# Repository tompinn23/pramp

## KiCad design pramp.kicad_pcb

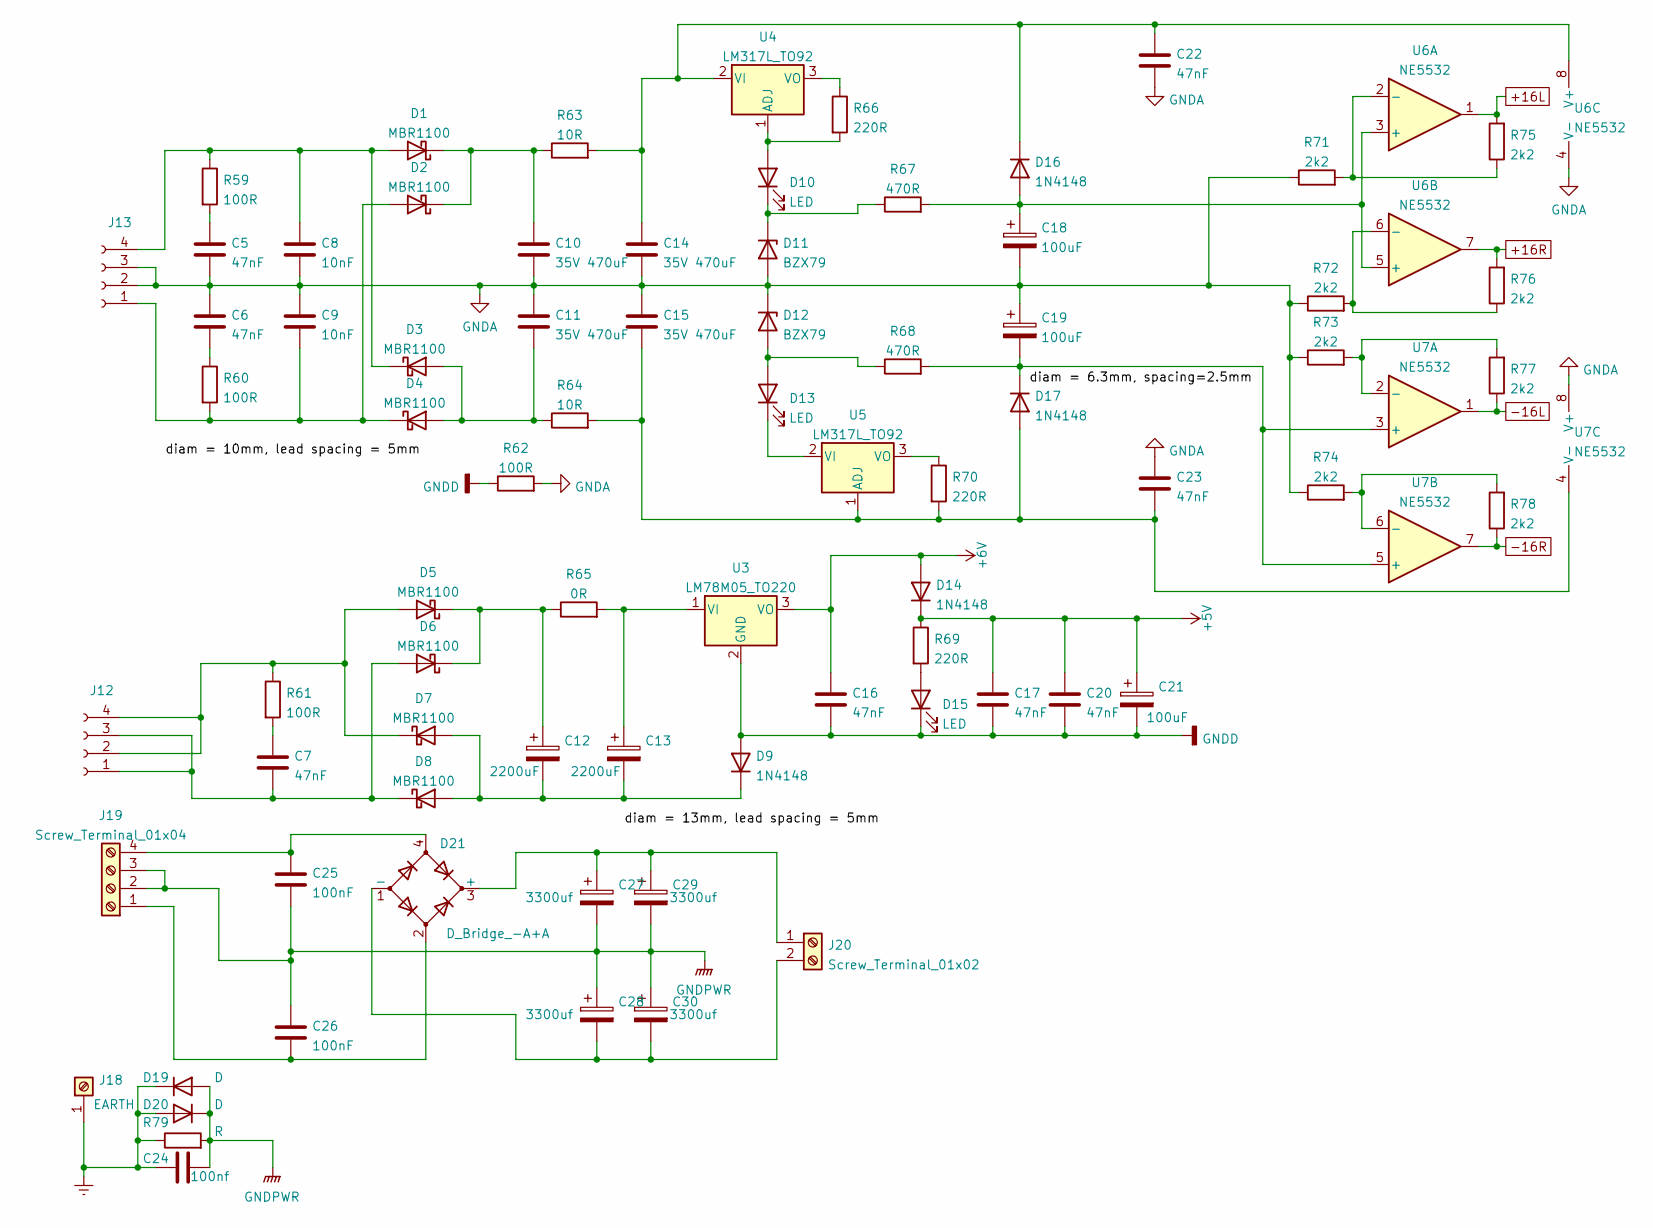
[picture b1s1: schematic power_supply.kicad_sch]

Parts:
C5, C6, C7, C16, C17, C20, C22, C23: 47nF; C_Disc_D3.8mm_W2.6mm_P2.50mm; Farnell part number 1216437
C8, C9: 10nF; C_Disc_D3.8mm_W2.6mm_P2.50mm; Farnell part number 1100380
C10, C11, C14, C15: 35V 470uF; CP_Radial_D10.0mm_P5.00mm; Farnell part number cpc
C12, C13: 2200uF; CP_Radial_D13.0mm_P5.00mm; Farnell part number 1219464
C18, C19, C21: 100uF; CP_Radial_D6.3mm_P2.50mm; Farnell part number 2841913
C24: 100nf; C_Disc_D16.0mm_W5.0mm_P10.00mm; Farnell part number 3289419
C25, C26: 100nF; C_Disc_D3.8mm_W2.6mm_P2.50mm; Farnell part number n.a
C27, C28, C29, C30: 3300uf; CP_Radial_D18.0mm_P7.50mm; Farnell part number n.a
D1, D2, D3, D4, D5, D6, D7, D8: MBR1100; D_DO-41_SOD81_P10.16mm_Horizontal; Farnell part number 1861419
D9, D14, D16, D17: 1N4148; D_DO-35_SOD27_P7.62mm_Horizontal; Farnell part number 1651145
D10, D13, D15: LED; LED_D3.0mm; Farnell part number 1142514
D11, D12: BZX79; D_DO-35_SOD27_P7.62mm_Horizontal; Farnell part number 1097241
D19, D20: D; TO-220-2_Vertical; Farnell part number 1885721
D21: D_Bridge_-A+A; Diode_Bridge_32.0x5.6x17.0mm_P10.0mm_P7.5mm; Farnell part number n.a
J12: 2x9v 7va; PinHeader_1x04_P2.54mm_Vertical
J13: 2x15v 4va; PinHeader_1x04_P2.54mm_Vertical
J18: EARTH; Pin_D1.0mm_L10.0mm_LooseFit; Farnell part number CN19743
J19: Screw_Terminal_01x04; JST_NV_B04P-NV_1x04_P5.00mm_Vertical; Farnell part number CN19747
J20: Screw_Terminal_01x02; JST_NV_B02P-NV_1x02_P5.00mm_Vertical
R59, R60, R61, R62: 100R; R_MELF_MMB-0207; Farnell part number 3086720
R63, R64: 10R; R_MELF_MMB-0207; Farnell part number 3086604
R65: 0R; R_MELF_MMB-0207; Farnell part number 3086471
R66, R69, R70: 220R; R_MELF_MMB-0207; Farnell part number 3086768
R67, R68: 470R; R_MELF_MMB-0207; Farnell part number 3086800
R71, R72, R73, R74, R75, R76, R77, R78: 2k2; R_MELF_MMB-0207; Farnell part number 3086884
R79: R; R_Axial_DIN0918_L18.0mm_D9.0mm_P25.40mm_Horizontal; Farnell part number 1735131
U3: LM78M05_TO220; TO-220-3_Horizontal_TabUp; Farnell part number 9666095
U4, U5: LM317L_TO92; TO-92_Inline; Farnell part number 3130111
U6, U7: NE5532; DIP-8_W7.62mm_Socket; Farnell part number 3117310

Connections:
+5V: C17.1, C20.1, C21.1, D14.1 (K), R69.1; also elsewhere on the board
+6V: C16.1, D14.2 (A), U3.3 (VO); also elsewhere on the board
+16L: R75.2, U6.1; also elsewhere on the board
+16R: R76.2, U6.7; also elsewhere on the board
-16L: R77.1, U7.1; also elsewhere on the board
-16R: R78.1, U7.7; also elsewhere on the board
Earth: C24.1, D19.1 (K), D20.2 (A), J18.1, R79.1
GNDA: C5.2, C6.1, C8.2, C9.1, C10.2, C11.1, C14.2, C15.1, C18.2, C19.1, C22.2, C23.1, D11.2 (A), D12.1 (K), J13.2, J13.3, R62.2, R71.1, R72.1, R73.1, R74.1, U6.4 (V-), U7.8 (V+); also elsewhere on the board
GNDD: C16.2, C17.2, C20.2, C21.2, D9.2 (A), D15.1 (K), R62.1, U3.2 (GND); also elsewhere on the board
GNDPWR: C24.2, C25.2, C26.1, C27.2, C28.1, C29.2, C30.1, D19.2 (A), D20.1 (K), J19.2, J19.3, R79.2
unnamed: C5.1, R59.2
unnamed: C6.2, R60.1
unnamed: C7.1, R61.2
unnamed: C7.2, D6.2 (A), D8.1 (K), J12.1, J12.3
unnamed: C8.1, D1.2 (A), D3.1 (K), J13.4, R59.1
unnamed: C9.2, D2.2 (A), D4.1 (K), J13.1, R60.2
unnamed: C10.1, D1.1 (K), D2.1 (K), R63.1
unnamed: C11.2, D3.2 (A), D4.2 (A), R64.1
unnamed: C12.1, D5.1 (K), D6.1 (K), R65.1
unnamed: C12.2, C13.2, D7.2 (A), D8.2 (A), D9.1 (K)
unnamed: C13.1, R65.2, U3.1 (VI)
unnamed: C14.1, C22.1, D16.1 (K), R63.2, U4.2 (VI), U6.8 (V+)
unnamed: C15.2, C23.2, D17.2 (A), R64.2, R70.2, U5.1 (ADJ), U7.4 (V-)
unnamed: C18.1, D16.2 (A), R67.2, U6.3 (+), U6.5 (+)
unnamed: C19.2, D17.1 (K), R68.2, U7.3 (+), U7.5 (+)
unnamed: C25.1, D21.4, J19.4
unnamed: C26.2, D21.2, J19.1
unnamed: C27.1, C29.1, D21.3 (+), J20.1
unnamed: C28.2, C30.2, D21.1 (-), J20.2
unnamed: D5.2 (A), D7.1 (K), J12.2, J12.4, R61.1
unnamed: D10.1 (K), D11.1 (K), R67.1
unnamed: D10.2 (A), R66.2, U4.1 (ADJ)
unnamed: D12.2 (A), D13.2 (A), R68.1
unnamed: D13.1 (K), U5.2 (VI)
unnamed: D15.2 (A), R69.2
unnamed: R66.1, U4.3 (VO)
unnamed: R70.1, U5.3 (VO)
unnamed: R71.2, R75.1, U6.2 (-)
unnamed: R72.2, R76.1, U6.6 (-)
unnamed: R73.2, R77.2, U7.2 (-)
unnamed: R74.2, R78.2, U7.6 (-)

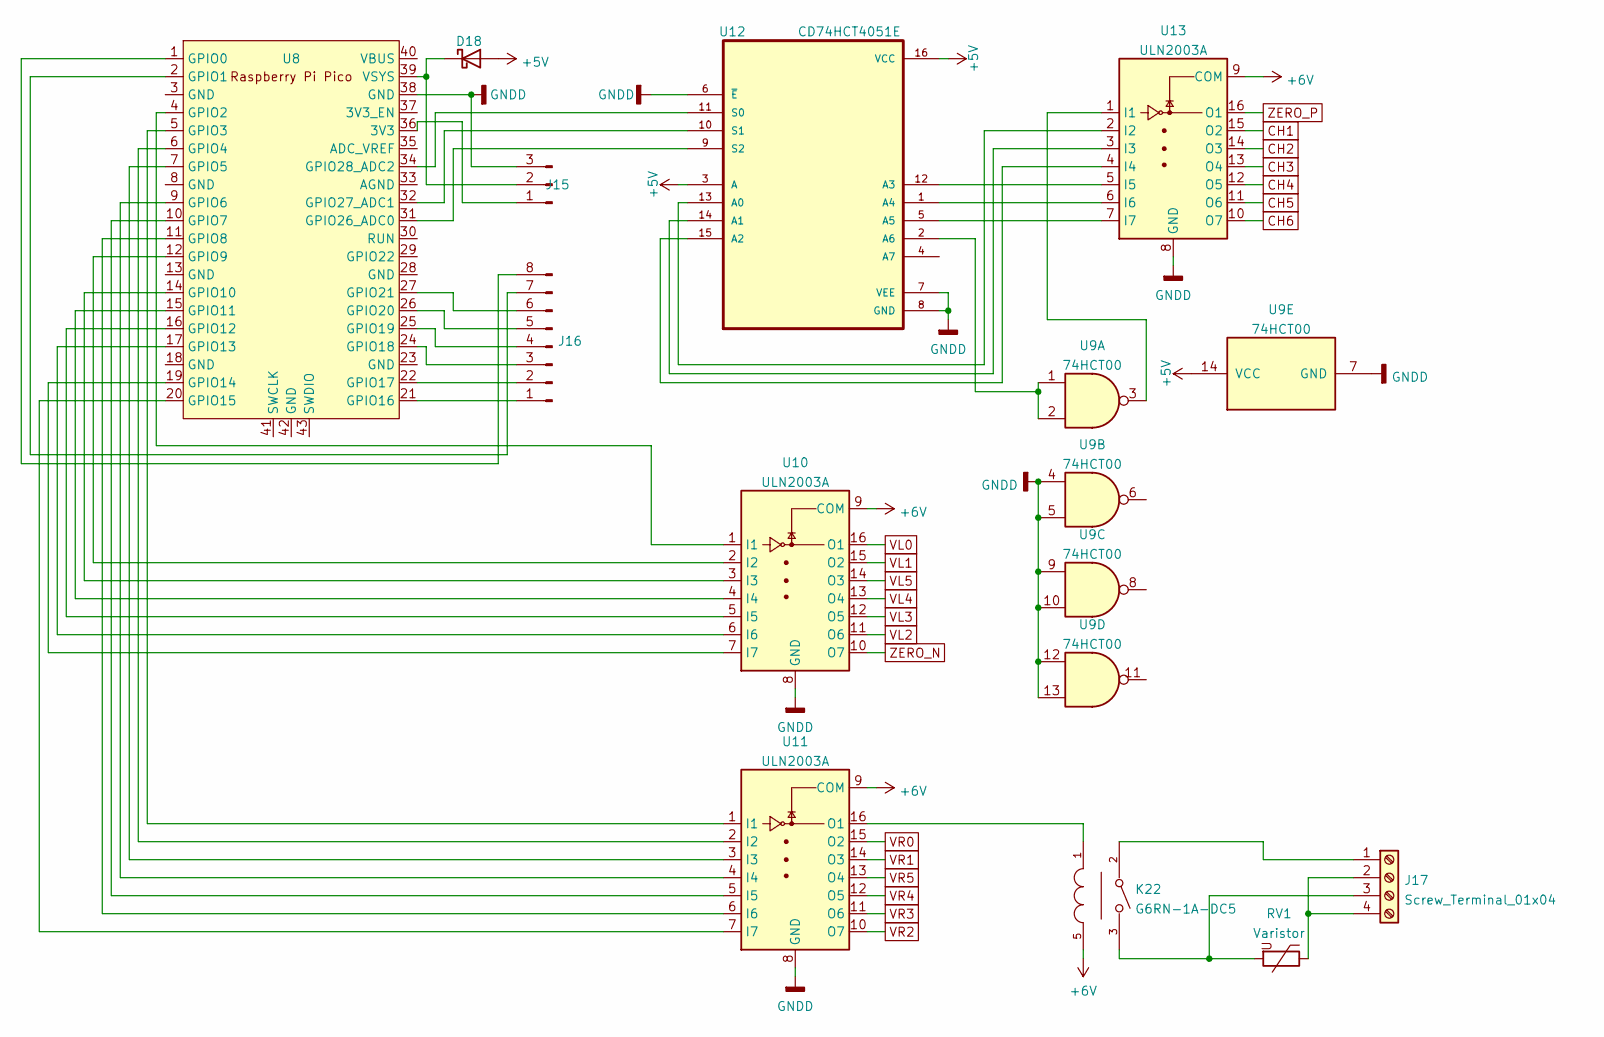
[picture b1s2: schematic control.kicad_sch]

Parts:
D18: D_Schottky; D_DO-41_SOD81_P10.16mm_Horizontal; Farnell part number 1861419
J15: AUX_D_PWR; PinHeader_1x03_P2.54mm_Vertical
J16: AUX_GPIO; PinHeader_1x08_P2.54mm_Vertical
J17: Screw_Terminal_01x04; JST_NV_B04P-NV_1x04_P5.00mm_Vertical; Farnell part number CN19747
K22: G6RN-1A-DC5; Omron-G6RN-1A-DC5-MFG; coil voltage 5V; current rating 8A; mouser part number 653-G6RN-1A-DC5; digikey description RELAY GENERAL PURPOSE SPST 8A 5V
RV1: Varistor; RV_Disc_D7mm_W4.2mm_P5mm; Farnell part number 1004290
U8: Pico; RPi_Pico_SMD_TH
U9: 74HCT00; DIP-14_W7.62mm; Farnell part number 3120419
U10, U11, U13: ULN2003A; DIP-18_W7.62mm; Farnell part number 1094421
U12: CD74HCT4051E; DIP794W45P254L1969H508Q16; Farnell part number 3009605

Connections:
+5V: D18.2 (A), U9.14 (VCC), U12.3 (A), U12.16 (VCC); also elsewhere on the board
+6V: K22.5, U10.9 (COM), U11.9 (COM), U13.9 (COM); also elsewhere on the board
CH1: U13.15 (O2); also elsewhere on the board
CH2: U13.14 (O3); also elsewhere on the board
CH3: U13.13 (O4); also elsewhere on the board
CH4: U13.12 (O5); also elsewhere on the board
CH5: U13.11 (O6); also elsewhere on the board
CH6: U13.10 (O7); also elsewhere on the board
GNDD: J15.3, U8.38 (GND), U9.4, U9.5, U9.7 (GND), U9.9, U9.10, U9.12, U9.13, U10.8 (GND), U11.8 (GND), U12.6 (~E), U12.7 (VEE), U12.8 (GND), U13.8 (GND); also elsewhere on the board
unnamed: D18.1 (K), J15.2, U8.39 (VSYS)
unnamed: J15.1, U8.36 (3V3)
unnamed: J16.1, U8.21 (GPIO16)
unnamed: J16.2, U8.22 (GPIO17)
unnamed: J16.3, U8.24 (GPIO18)
unnamed: J16.4, U8.25 (GPIO19)
unnamed: J16.5, U8.26 (GPIO20)
unnamed: J16.6, U8.27 (GPIO21)
unnamed: J16.7, U8.2 (GPIO1)
unnamed: J16.8, U8.1 (GPIO0)
unnamed: J17.1, K22.2
unnamed: J17.2, J17.4, RV1.1
unnamed: J17.3, K22.3, RV1.2
unnamed: K22.1, U11.16 (O1)
unnamed: U8.4 (GPIO2), U10.1 (I1)
unnamed: U8.12 (GPIO9), U10.2 (I2)
unnamed: U8.14 (GPIO10), U10.3 (I3)
unnamed: U8.15 (GPIO11), U10.4 (I4)
unnamed: U8.16 (GPIO12), U10.5 (I5)
unnamed: U8.17 (GPIO13), U10.6 (I6)
unnamed: U8.19 (GPIO14), U10.7 (I7)
unnamed: U8.5 (GPIO3), U11.1 (I1)
unnamed: U8.6 (GPIO4), U11.2 (I2)
unnamed: U8.7 (GPIO5), U11.3 (I3)
unnamed: U8.9 (GPIO6), U11.4 (I4)
unnamed: U8.10 (GPIO7), U11.5 (I5)
unnamed: U8.11 (GPIO8), U11.6 (I6)
unnamed: U8.20 (GPIO15), U11.7 (I7)
unnamed: U12.1 (A4), U13.6 (I6)
unnamed: U9.1, U9.2, U12.2 (A6)
unnamed: U12.5 (A5), U13.7 (I7)
unnamed: U8.31 (GPIO26_ADC0), U12.9 (S2)
unnamed: U8.32 (GPIO27_ADC1), U12.10 (S1)
unnamed: U8.34 (GPIO28_ADC2), U12.11 (S0)
unnamed: U12.12 (A3), U13.5 (I5)
unnamed: U12.13 (A0), U13.2 (I2)
unnamed: U12.14 (A1), U13.3 (I3)
unnamed: U12.15 (A2), U13.4 (I4)
unnamed: U9.3, U13.1 (I1)
VL0: U10.16 (O1); also elsewhere on the board
VL1: U10.15 (O2); also elsewhere on the board
VL2: U10.11 (O6); also elsewhere on the board
VL3: U10.12 (O5); also elsewhere on the board
VL4: U10.13 (O4); also elsewhere on the board
VL5: U10.14 (O3); also elsewhere on the board
VR0: U11.15 (O2); also elsewhere on the board
VR1: U11.14 (O3); also elsewhere on the board
VR2: U11.10 (O7); also elsewhere on the board
VR3: U11.11 (O6); also elsewhere on the board
VR4: U11.12 (O5); also elsewhere on the board
VR5: U11.13 (O4); also elsewhere on the board
ZERO_N: U10.10 (O7); also elsewhere on the board
ZERO_P: U13.16 (O1); also elsewhere on the board

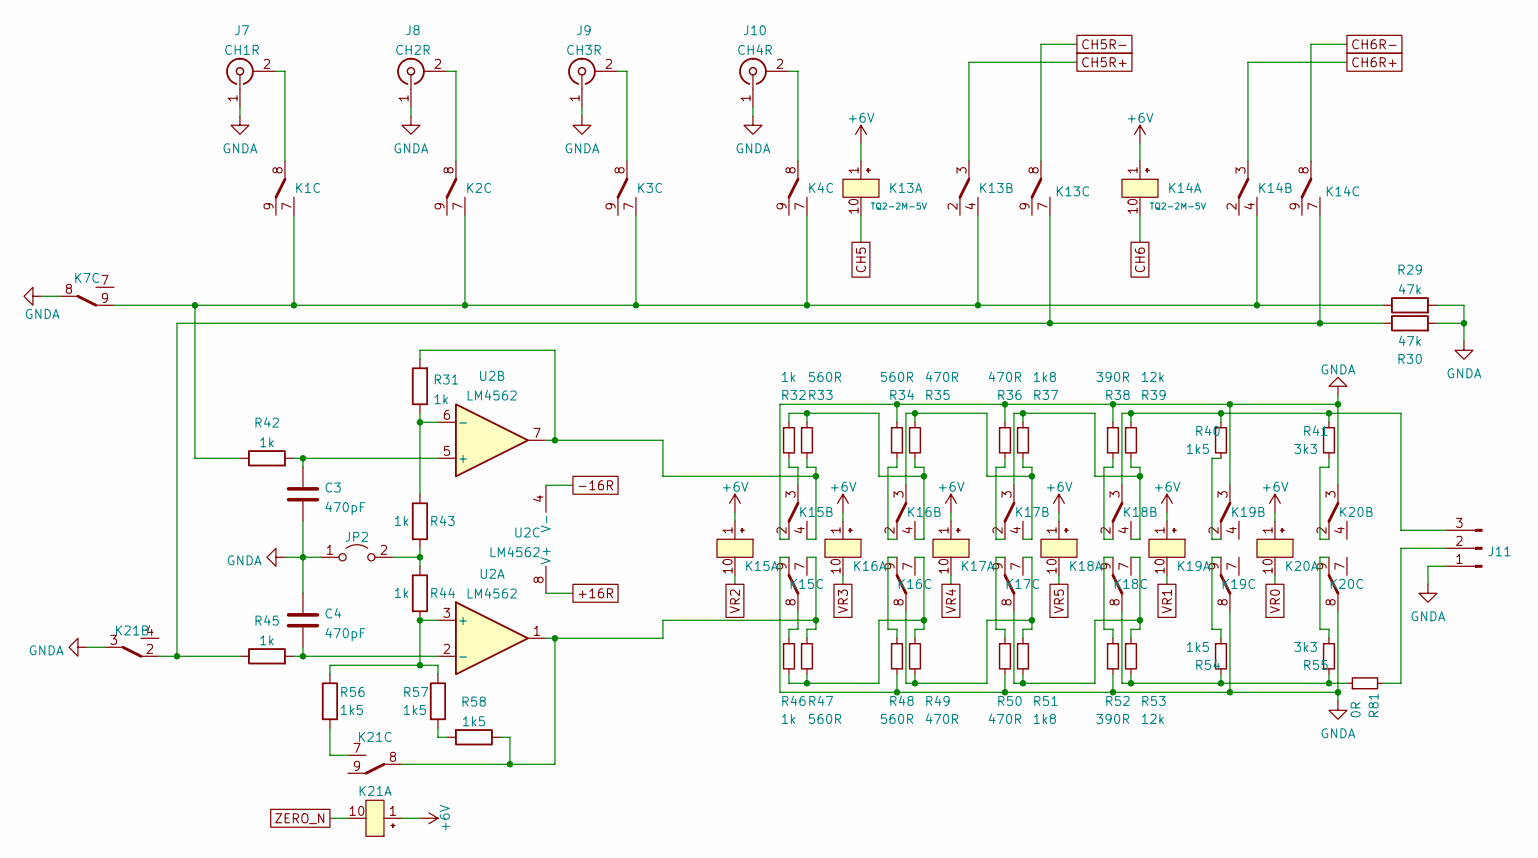
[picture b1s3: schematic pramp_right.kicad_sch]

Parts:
C3, C4: 470pF; C_Disc_D3.8mm_W2.6mm_P2.50mm; Farnell part number 1141769
J7: CH1R; SolderWire-0.1sqmm_1x02_P3.6mm_D0.4mm_OD1mm
J8: CH2R; SolderWire-0.1sqmm_1x02_P3.6mm_D0.4mm_OD1mm
J9: CH3R; SolderWire-0.1sqmm_1x02_P3.6mm_D0.4mm_OD1mm
J10: CH4R; SolderWire-0.1sqmm_1x02_P3.6mm_D0.4mm_OD1mm
J11: L_OUT; JST_EH_B3B-EH-A_1x03_P2.50mm_Vertical
JP2: Jumper_2_Open; PinHeader_1x02_P2.54mm_Vertical
K1, K2, K3, K4, K7, K13, K14, K15, K16, K17, K18, K19, K20, K21: TQ2-2M-5V; TQ2-5V
R29, R30: 47k; R_MELF_MMB-0207; Farnell part number 2838229
R31, R32, R42, R43, R44, R45, R46: 1k; R_MELF_MMB-0207; Farnell part number 3086847
R33, R34, R47, R48: 560R; R_MELF_MMB-0207; Farnell part number 3086811
R35, R36, R49, R50: 470R; R_MELF_MMB-0207; Farnell part number 3086800
R37, R51: 1k8; R_MELF_MMB-0207; Farnell part number 3086872
R38, R52: 390R; R_MELF_MMB-0207; Farnell part number 3086793
R39, R53: 12k; R_MELF_MMB-0207; Farnell part number 2838151
R40, R54, R56, R57, R58: 1k5; R_MELF_MMB-0207; Farnell part number 3086860
R41, R55: 3k3; R_MELF_MMB-0207; Farnell part number 3086902
R81: 0R; R_MELF_MMB-0207; Farnell part number 3086471
U2: LM4562; DIP-8_W7.62mm_Socket; Farnell part number 3116891

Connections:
+6V: K13.1, K14.1, K15.1, K16.1, K17.1, K18.1, K19.1, K20.1, K21.1; also elsewhere on the board
+16R: U2.8 (V+); also elsewhere on the board
-16R: U2.4 (V-); also elsewhere on the board
CH5: K13.10; also elsewhere on the board
CH5R+: K13.3; also elsewhere on the board
CH5R-: K13.8; also elsewhere on the board
CH6: K14.10; also elsewhere on the board
CH6R+: K14.3; also elsewhere on the board
CH6R-: K14.8; also elsewhere on the board
GNDA: C3.2, C4.1, J7.1 (In), J8.1 (In), J9.1 (In), J10.1 (In), J11.1, JP2.1 (A), K7.8, K15.2, K15.9, K19.3, K19.8, K20.3, K20.8, K21.3, R29.2, R30.2, R34.1, R36.1, R38.1, R48.2, R50.2, R52.2; also elsewhere on the board
unnamed: C3.1, R42.2, U2.5 (+)
unnamed: C4.2, R45.2, U2.2 (-)
unnamed: J7.2 (Ext), K1.8
unnamed: J8.2 (Ext), K2.8
unnamed: J9.2 (Ext), K3.8
unnamed: J10.2 (Ext), K4.8
unnamed: J11.2, R81.2
unnamed: J11.3, K18.3, R39.1, R40.1, R41.1
unnamed: JP2.2 (B), R43.2, R44.1
unnamed: K1.7, K2.7, K3.7, K4.7, K7.9, K13.4, K14.4, R29.1, R42.1
unnamed: K13.7, K14.7, K21.2, R30.1, R45.1
unnamed: K15.3, R32.2
unnamed: K15.4, R31.2, R33.2, U2.7
unnamed: K15.7, K21.8, R47.1, R58.1, U2.1
unnamed: K15.8, R46.1
unnamed: K16.2, R34.2
unnamed: K16.3, K17.4, R35.1, R37.2
unnamed: K16.4, R32.1, R33.1, R35.2
unnamed: K16.7, R46.2, R47.2, R49.1
unnamed: K16.8, K17.7, R49.2, R51.1
unnamed: K16.9, R48.1
unnamed: K17.2, R36.2
unnamed: K17.3, K18.4, R37.1, R39.2
unnamed: K17.8, K18.7, R51.2, R53.1
unnamed: K17.9, R50.1
unnamed: K18.2, R38.2
unnamed: K18.8, R53.2, R54.2, R55.2, R81.1
unnamed: K18.9, R52.1
unnamed: K19.2, R40.2
unnamed: K19.9, R54.1
unnamed: K20.2, R41.2
unnamed: K20.9, R55.1
unnamed: K21.7, R56.2
unnamed: R31.1, R43.1, U2.6 (-)
unnamed: R44.2, R56.1, R57.1, U2.3 (+)
unnamed: R57.2, R58.2
VR0: K20.10; also elsewhere on the board
VR1: K19.10; also elsewhere on the board
VR2: K15.10; also elsewhere on the board
VR3: K16.10; also elsewhere on the board
VR4: K17.10; also elsewhere on the board
VR5: K18.10; also elsewhere on the board
ZERO_N: K21.10; also elsewhere on the board

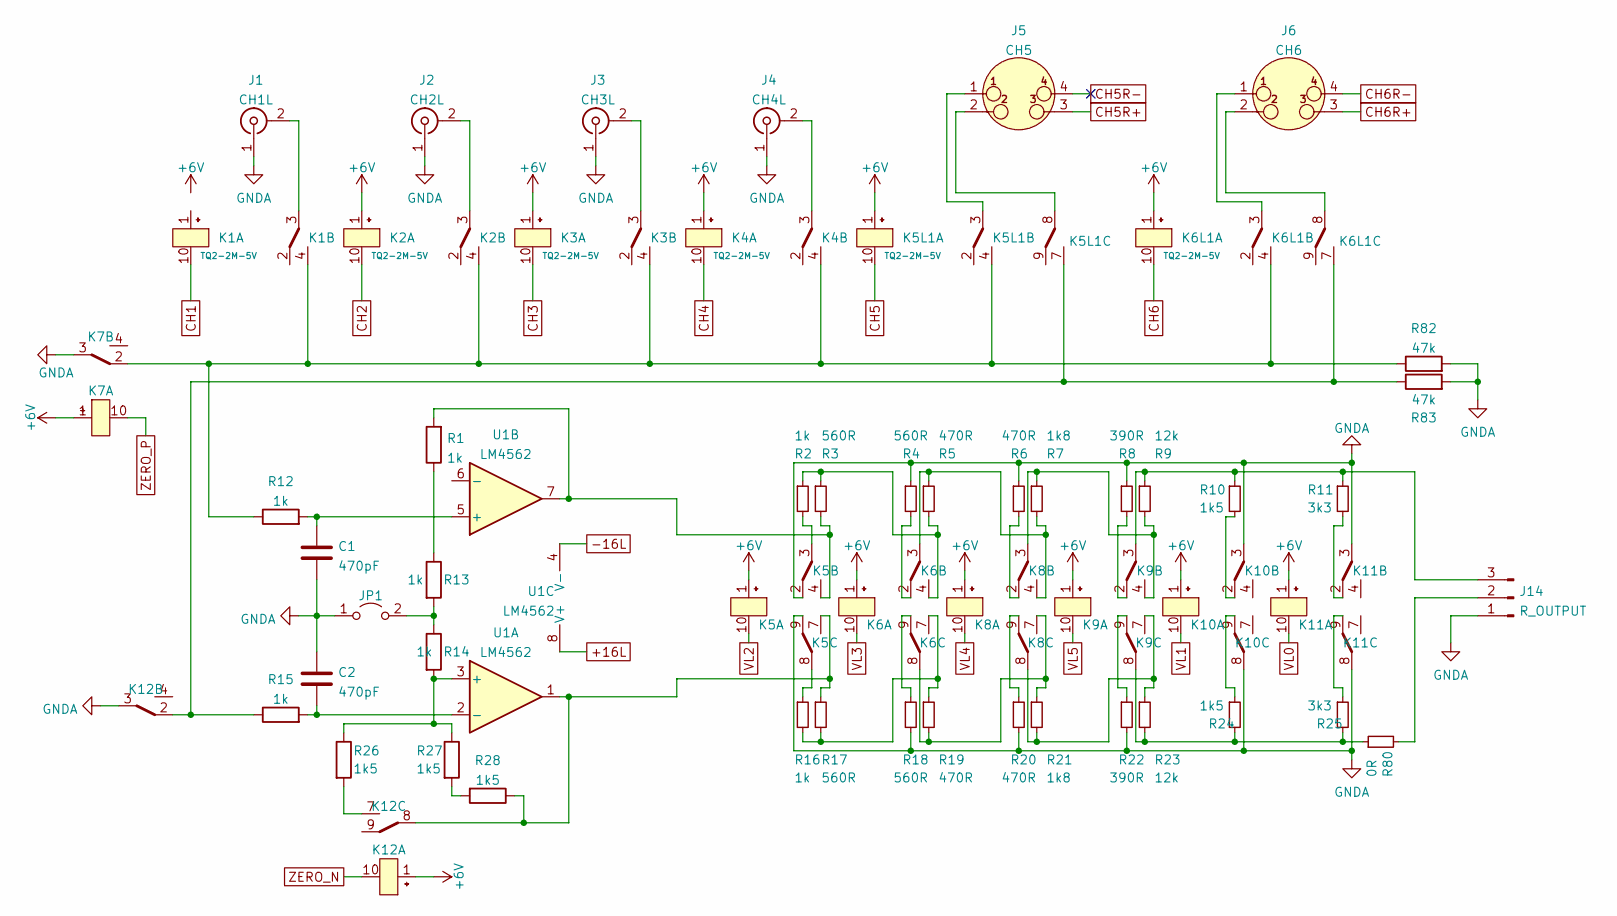
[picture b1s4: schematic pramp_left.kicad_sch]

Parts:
C1, C2: 470pF; C_Disc_D3.8mm_W2.6mm_P2.50mm; Farnell part number 1141769
J1: CH1L; SolderWire-0.1sqmm_1x02_P3.6mm_D0.4mm_OD1mm
J2: CH2L; SolderWire-0.1sqmm_1x02_P3.6mm_D0.4mm_OD1mm
J3: CH3L; SolderWire-0.1sqmm_1x02_P3.6mm_D0.4mm_OD1mm
J4: CH4L; SolderWire-0.1sqmm_1x02_P3.6mm_D0.4mm_OD1mm
J5: CH5; SolderWire-0.1sqmm_1x04_P3.6mm_D0.4mm_OD1mm
J6: CH6; SolderWire-0.1sqmm_1x04_P3.6mm_D0.4mm_OD1mm
J14: R_OUTPUT; JST_EH_B3B-EH-A_1x03_P2.50mm_Vertical; Farnell part number CN21573
JP1: Jumper_2_Open; PinHeader_1x02_P2.54mm_Vertical
K1, K2, K3, K4, K5, K5L1, K6, K6L1, K7, K8, K9, K10, K11, K12: TQ2-2M-5V; TQ2-5V
R1, R2, R12, R13, R14, R15, R16: 1k; R_MELF_MMB-0207; Farnell part number 3086847
R3, R4, R17, R18: 560R; R_MELF_MMB-0207; Farnell part number 3086811
R5, R6, R19, R20: 470R; R_MELF_MMB-0207; Farnell part number 3086800
R7, R21: 1k8; R_MELF_MMB-0207; Farnell part number 3086872
R8, R22: 390R; R_MELF_MMB-0207; Farnell part number 3086793
R9, R23: 12k; R_MELF_MMB-0207; Farnell part number 2838151
R10, R24, R26, R27, R28: 1k5; R_MELF_MMB-0207; Farnell part number 3086860
R11, R25: 3k3; R_MELF_MMB-0207; Farnell part number 3086902
R80: 0R; R_MELF_MMB-0207; Farnell part number 3086471
R82, R83: 47k; R_MELF_MMB-0207; Farnell part number 2838229
U1: LM4562; DIP-8_W7.62mm_Socket; Farnell part number 3116891

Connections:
+6V: K2.1, K3.1, K4.1, K5.1, K5L1.1, K6.1, K6L1.1, K7.1, K8.1, K9.1, K10.1, K11.1, K12.1; also elsewhere on the board
+16L: U1.8 (V+); also elsewhere on the board
-16L: U1.4 (V-); also elsewhere on the board
CH1: K1.10; also elsewhere on the board
CH2: K2.10; also elsewhere on the board
CH3: K3.10; also elsewhere on the board
CH4: K4.10; also elsewhere on the board
CH5: K5L1.10; also elsewhere on the board
CH5R+: J5.3; also elsewhere on the board
CH5R-: J5.4; also elsewhere on the board
CH6: K6L1.10; also elsewhere on the board
CH6R+: J6.3; also elsewhere on the board
CH6R-: J6.4; also elsewhere on the board
GNDA: C1.2, C2.1, J1.1 (In), J2.1 (In), J3.1 (In), J4.1 (In), J14.1, JP1.1 (A), K5.2, K5.9, K7.3, K10.3, K10.8, K11.3, K11.8, K12.3, R4.1, R6.1, R8.1, R18.2, R20.2, R22.2, R82.2, R83.2; also elsewhere on the board
unnamed: C1.1, R12.2, U1.5 (+)
unnamed: C2.2, R15.2, U1.2 (-)
unnamed: J1.2 (Ext), K1.3
unnamed: J2.2 (Ext), K2.3
unnamed: J3.2 (Ext), K3.3
unnamed: J4.2 (Ext), K4.3
unnamed: J5.1, K5L1.3
unnamed: J5.2, K5L1.8
unnamed: J6.1, K6L1.3
unnamed: J6.2, K6L1.8
unnamed: J14.2, R80.2
unnamed: J14.3, K9.3, R9.1, R10.1, R11.1
unnamed: JP1.2 (B), R13.2, R14.1
unnamed: K1.4, K2.4, K3.4, K4.4, K5L1.4, K6L1.4, K7.2, R12.1, R82.1
unnamed: K5.3, R2.2
unnamed: K5.4, R1.2, R3.2, U1.7
unnamed: K5.8, R16.1
unnamed: K6.2, R4.2
unnamed: K6.3, K8.4, R5.1, R7.2
unnamed: K6.4, R2.1, R3.1, R5.2
unnamed: K6.7, R16.2, R17.2, R19.1
unnamed: K6.8, K8.7, R19.2, R21.1
unnamed: K6.9, R18.1
unnamed: K8.2, R6.2
unnamed: K8.3, K9.4, R7.1, R9.2
unnamed: K8.8, K9.7, R21.2, R23.1
unnamed: K8.9, R20.1
unnamed: K9.2, R8.2
unnamed: K9.8, R23.2, R24.2, R25.2, R80.1
unnamed: K9.9, R22.1
unnamed: K10.2, R10.2
unnamed: K10.9, R24.1
unnamed: K11.2, R11.2
unnamed: K11.9, R25.1
unnamed: K5L1.7, K6L1.7, K12.2, R15.1, R83.1
unnamed: K12.7, R26.2
unnamed: K5.7, K12.8, R17.1, R28.1, U1.1
unnamed: R1.1, R13.1
unnamed: R14.2, R26.1, R27.1, U1.3 (+)
unnamed: R27.2, R28.2
VL0: K11.10; also elsewhere on the board
VL1: K10.10; also elsewhere on the board
VL2: K5.10; also elsewhere on the board
VL3: K6.10; also elsewhere on the board
VL4: K8.10; also elsewhere on the board
VL5: K9.10; also elsewhere on the board
ZERO_N: K12.10; also elsewhere on the board
ZERO_P: K7.10; also elsewhere on the board

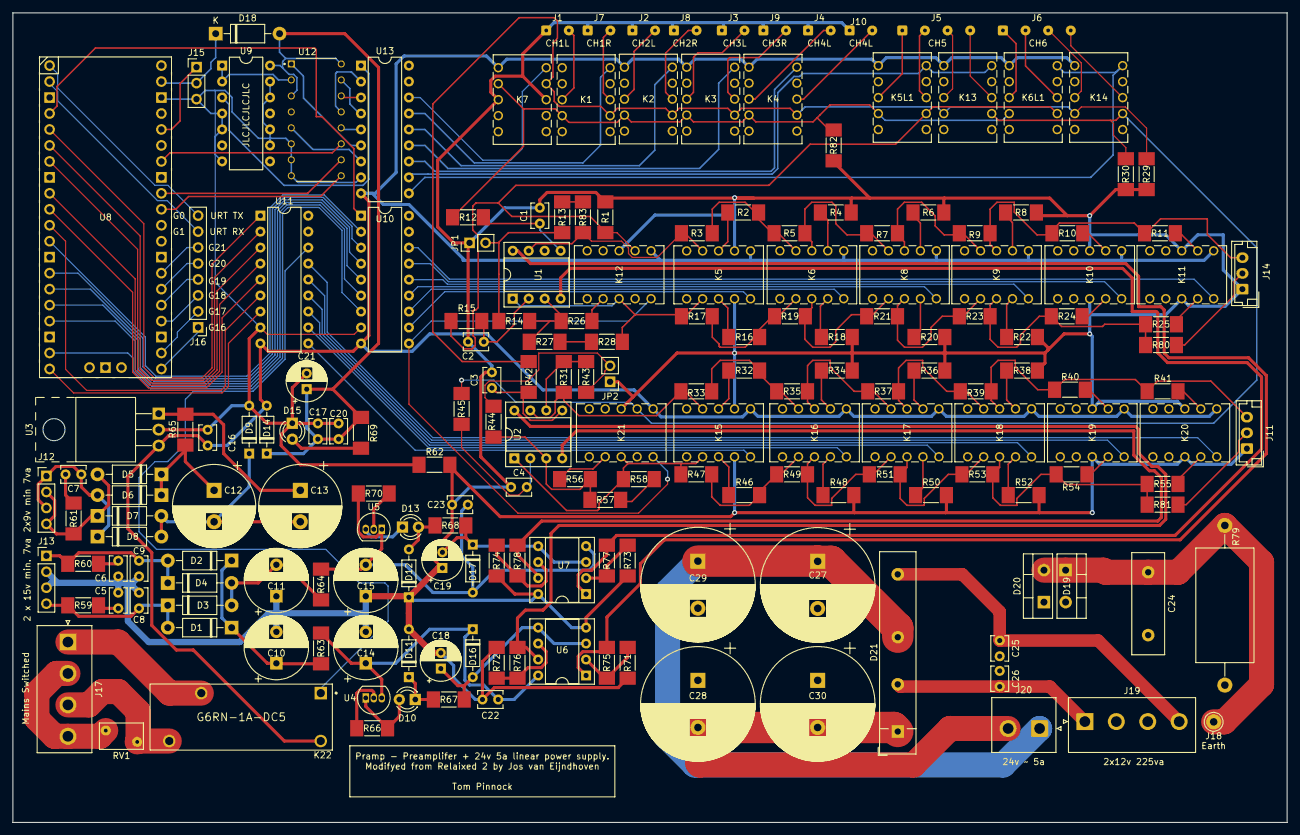
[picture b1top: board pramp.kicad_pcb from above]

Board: 2 copper layers, 202.7 x 128.8 mm, 194 parts (0 on the bottom side), 180 nets.

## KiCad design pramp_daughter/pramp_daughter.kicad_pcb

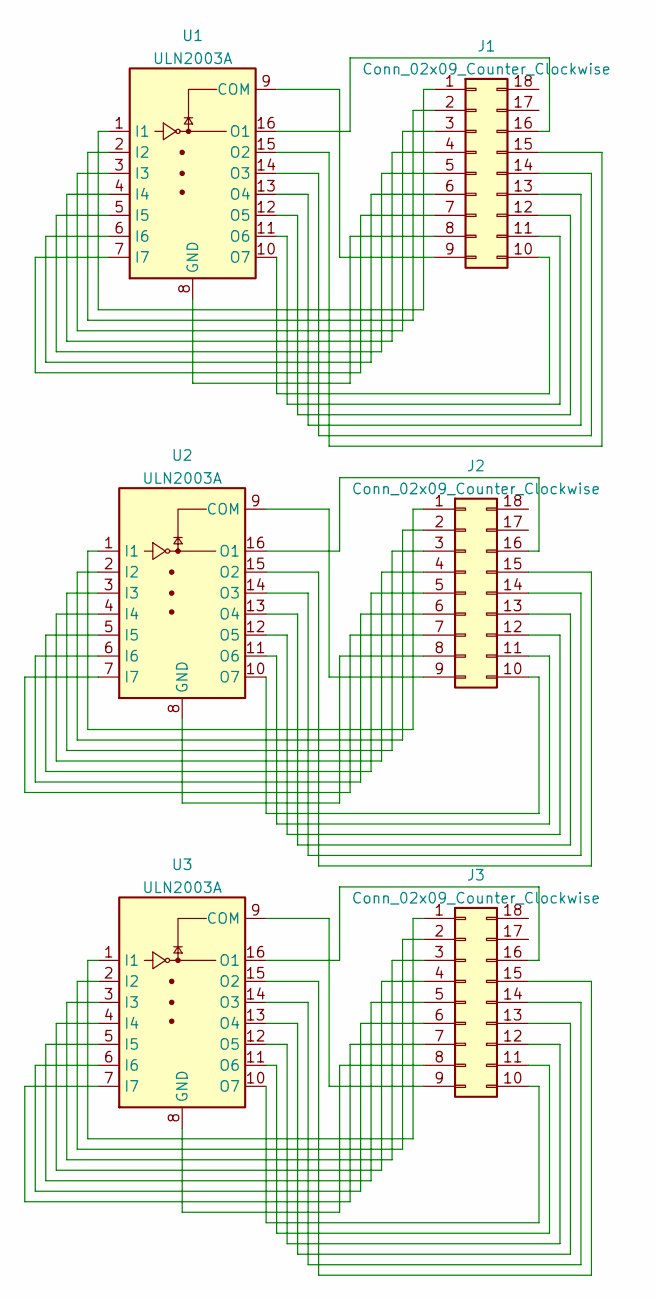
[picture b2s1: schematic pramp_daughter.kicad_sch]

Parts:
J1, J2, J3: Conn_02x09_Counter_Clockwise; DIP-18_W7.62mm
U1, U2, U3: ULN2003A; DIP-16_W7.62mm

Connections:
unnamed: J1.1, U1.1 (I1)
unnamed: J1.2, U1.2 (I2)
unnamed: J1.3, U1.3 (I3)
unnamed: J1.4, U1.4 (I4)
unnamed: J1.5, U1.5 (I5)
unnamed: J1.6, U1.6 (I6)
unnamed: J1.8, U1.8 (GND)
unnamed: J1.9, U1.9 (COM)
unnamed: J2.1, U2.1 (I1)
unnamed: J2.2, U2.2 (I2)
unnamed: J2.3, U2.3 (I3)
unnamed: J2.4, U2.4 (I4)
unnamed: J2.5, U2.5 (I5)
unnamed: J2.6, U2.6 (I6)
unnamed: J2.7, U2.7 (I7)
unnamed: J2.8, U2.8 (GND)
unnamed: J2.9, U2.9 (COM)
unnamed: J2.10, U2.10 (O7)
unnamed: J2.11, U2.11 (O6)
unnamed: J2.12, U2.12 (O5)
unnamed: J2.13, U2.13 (O4)
unnamed: J2.14, U2.14 (O3)
unnamed: J2.15, U2.15 (O2)
unnamed: J2.16, U2.16 (O1)
unnamed: J3.1, U3.1 (I1)
unnamed: J3.2, U3.2 (I2)
unnamed: J3.3, U3.3 (I3)
unnamed: J3.4, U3.4 (I4)
unnamed: J3.5, U3.5 (I5)
unnamed: J3.6, U3.6 (I6)
unnamed: J3.7, U3.7 (I7)
unnamed: J3.8, U3.8 (GND)
unnamed: J3.9, U3.9 (COM)
unnamed: J3.10, U3.10 (O7)
unnamed: J3.11, U3.11 (O6)
unnamed: J3.12, U3.12 (O5)
unnamed: J3.13, U3.13 (O4)
unnamed: J3.14, U3.14 (O3)
unnamed: J3.15, U3.15 (O2)
unnamed: J3.16, U3.16 (O1)
unnamed: J1.7, U1.7 (I7)
unnamed: J1.10, U1.10 (O7)
unnamed: J1.11, U1.11 (O6)
unnamed: J1.12, U1.12 (O5)
unnamed: J1.13, U1.13 (O4)
unnamed: J1.14, U1.14 (O3)
unnamed: J1.15, U1.15 (O2)
unnamed: J1.16, U1.16 (O1)

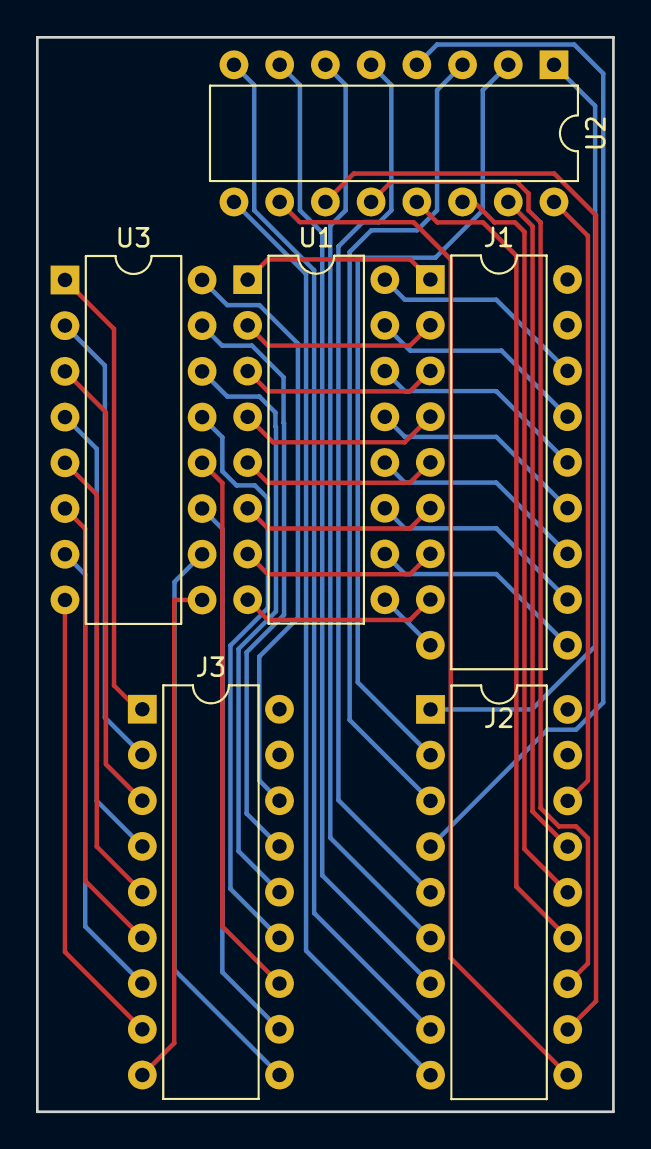
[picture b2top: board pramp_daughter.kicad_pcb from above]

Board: 2 copper layers, 32.0 x 59.7 mm, 6 parts (0 on the bottom side), 48 nets.

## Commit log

2022-11-20 Initial Commit
    Pramp v1.
